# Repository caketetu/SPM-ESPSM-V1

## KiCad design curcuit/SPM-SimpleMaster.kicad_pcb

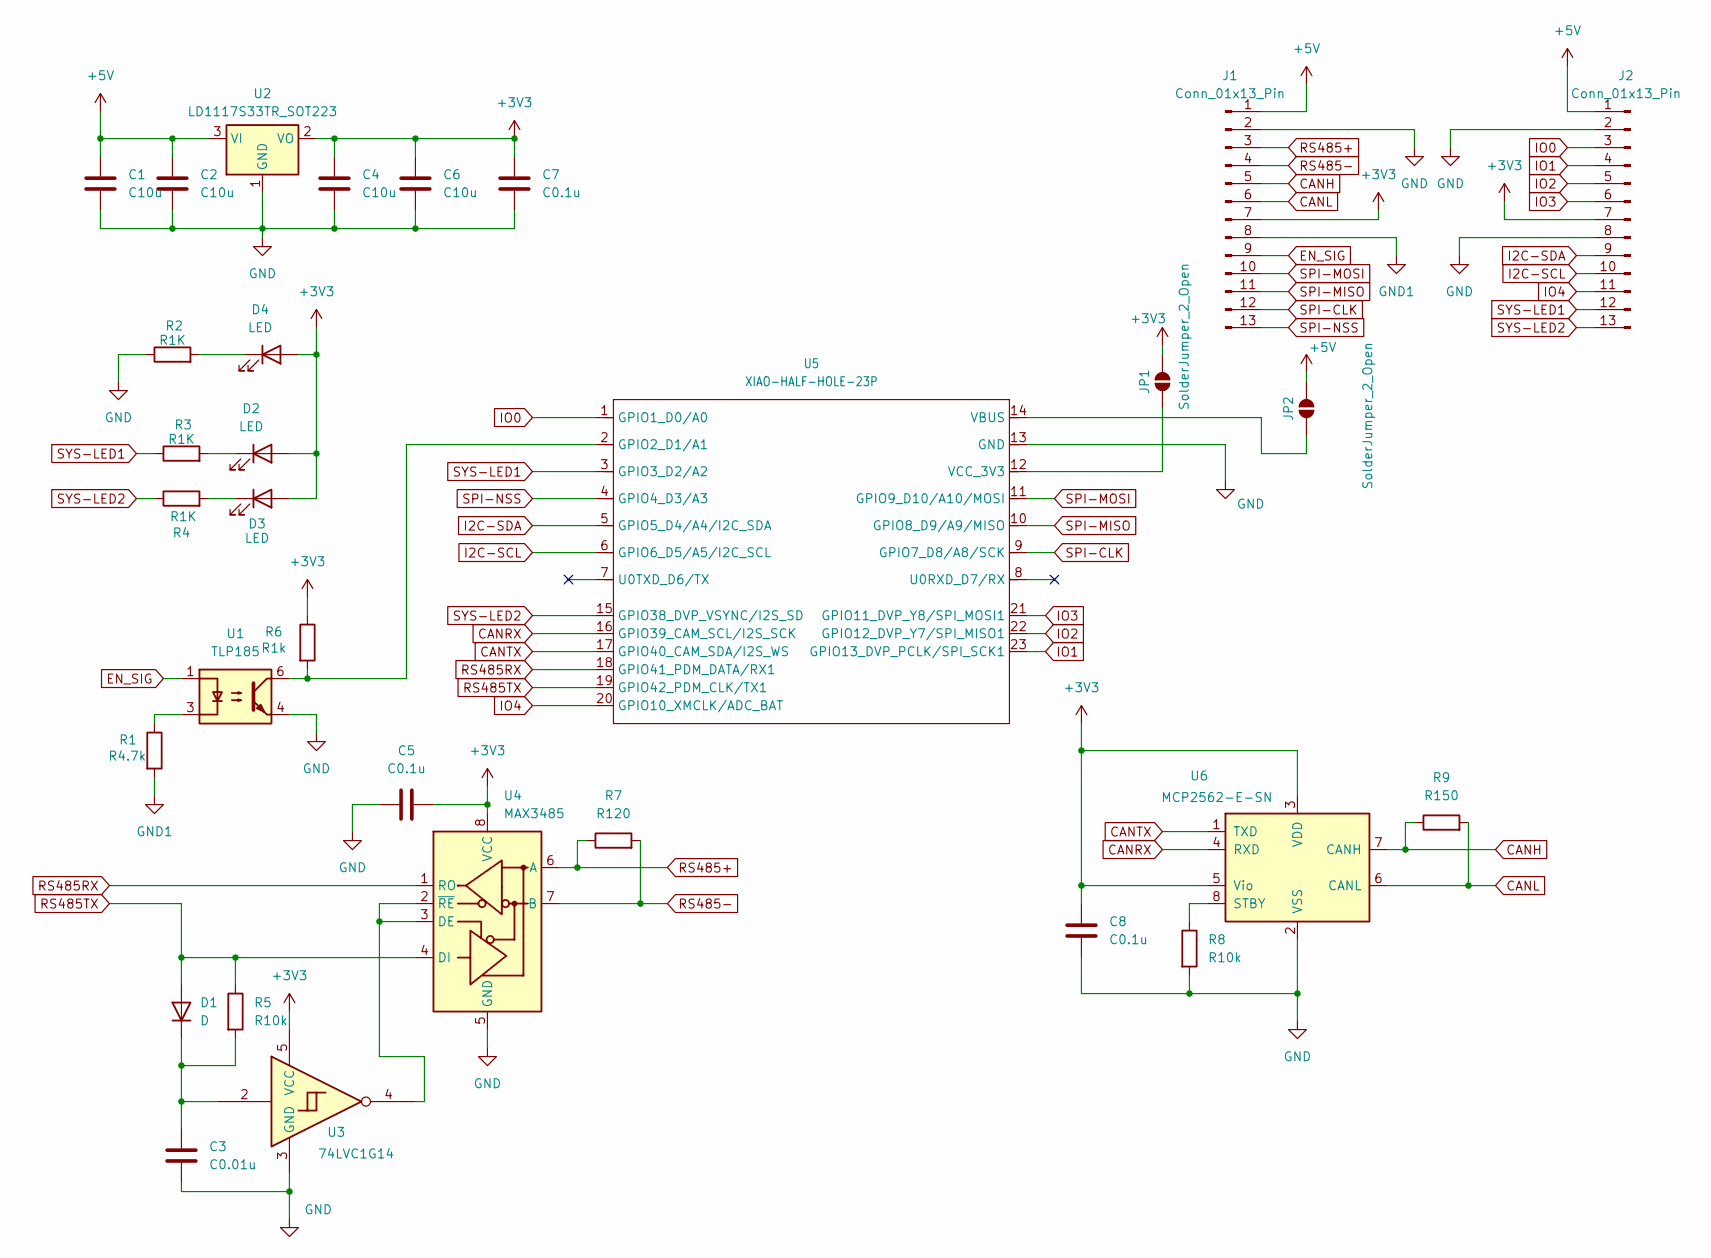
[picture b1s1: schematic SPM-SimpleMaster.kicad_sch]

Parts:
C1, C2, C4, C6: C10u; C_1206_3216Metric
C3: C0.01u; C_0805_2012Metric
C5, C7, C8: C0.1u; C_0603_1608Metric
D1: D; D_1206_3216Metric
D2, D3, D4: LED; LED_0603_1608Metric
J1, J2: Conn_01x13_Pin; PinSocket_1x13_P2.54mm_Vertical
JP1, JP2: SolderJumper_2_Open; SolderJumper-2_P1.3mm_Open_Pad1.0x1.5mm
R1: R4.7k; R_0603_1608Metric
R2, R3, R4: R1K; R_0603_1608Metric
R5, R8: R10k; R_0603_1608Metric
R6: R1k; R_0603_1608Metric
R7: R120; R_1206_3216Metric
R9: R150; R_1206_3216Metric
U1: TLP185; SOIC-4_4.55x3.7mm_P2.54mm
U2: LD1117S33TR_SOT223; SOT-223-3_TabPin2
U3: 74LVC1G14; SOT-23-5
U4: MAX3485; SOIC-8_3.9x4.9mm_P1.27mm
U5: XIAO-HALF-HOLE-23P; MOUDLE23P-SMD-2.54-21X17.8MM.kicad_mod.kicad_sym
U6: MCP2562-E-SN; SOIC-8_3.9x4.9mm_P1.27mm

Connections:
+3V3: C4.1, C5.2, C6.1, C7.1, C8.1, D2.2 (A), D3.2 (A), D4.2 (A), J1.7, J2.7, JP1.2 (B), R6.1, U2.2 (VO), U3.5 (VCC), U4.8 (VCC), U6.3 (VDD), U6.5 (Vio)
+5V: C1.1, C2.1, J1.1, J2.1, JP2.2 (B), U2.3 (VI)
CANH: J1.5, R9.1, U6.7 (CANH)
CANL: J1.6, R9.2, U6.6 (CANL)
CANRX: U5.16 (GPIO39_CAM_SCL/I2S_SCK), U6.4 (RXD)
CANTX: U5.17 (GPIO40_CAM_SDA/I2S_WS), U6.1 (TXD)
EN_SIG: J1.9, U1.1
GND: C1.2, C2.2, C3.2, C4.2, C5.1, C6.2, C7.2, C8.2, J1.2, J2.2, J2.8, R2.1, R8.2, U1.4, U2.1 (GND), U3.3 (GND), U4.5 (GND), U5.13 (GND), U6.2 (VSS)
GND1: J1.8, R1.2
I2C-SCL: J2.10, U5.6 (GPIO6_D5/A5/I2C_SCL)
I2C-SDA: J2.9, U5.5 (GPIO5_D4/A4/I2C_SDA)
IO0: J2.3, U5.1 (GPIO1_D0/A0)
IO1: J2.4, U5.23 (GPIO13_DVP_PCLK/SPI_SCK1)
IO2: J2.5, U5.22 (GPIO12_DVP_Y7/SPI_MISO1)
IO3: J2.6, U5.21 (GPIO11_DVP_Y8/SPI_MOSI1)
IO4: J2.11, U5.20 (GPIO10_XMCLK/ADC_BAT)
unnamed: C3.1, D1.1 (K), R5.2, U3.2
unnamed: D2.1 (K), R3.2
unnamed: D3.1 (K), R4.2
unnamed: D4.1 (K), R2.2
unnamed: JP1.1 (A), U5.12 (VCC_3V3)
unnamed: JP2.1 (A), U5.14 (VBUS)
unnamed: R1.1, U1.3
unnamed: U3.4, U4.2 (~RE), U4.3 (DE)
unnamed: R6.2, U1.6, U5.2 (GPIO2_D1/A1)
unnamed: R8.1, U6.8 (STBY)
RS485+: J1.3, R7.1, U4.6 (A)
RS485-: J1.4, R7.2, U4.7 (B)
RS485RX: U4.1 (RO), U5.18 (GPIO41_PDM_DATA/RX1)
RS485TX: D1.2 (A), R5.1, U4.4 (DI), U5.19 (GPIO42_PDM_CLK/TX1)
SPI-CLK: J1.12, U5.9 (GPIO7_D8/A8/SCK)
SPI-MISO: J1.11, U5.10 (GPIO8_D9/A9/MISO)
SPI-MOSI: J1.10, U5.11 (GPIO9_D10/A10/MOSI)
SPI-NSS: J1.13, U5.4 (GPIO4_D3/A3)
SYS-LED1: J2.12, R3.1, U5.3 (GPIO3_D2/A2)
SYS-LED2: J2.13, R4.1, U5.15 (GPIO38_DVP_VSYNC/I2S_SD)

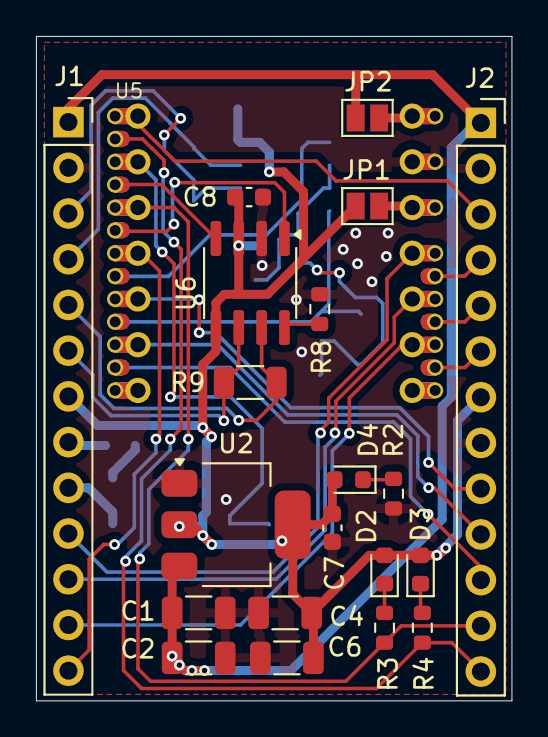
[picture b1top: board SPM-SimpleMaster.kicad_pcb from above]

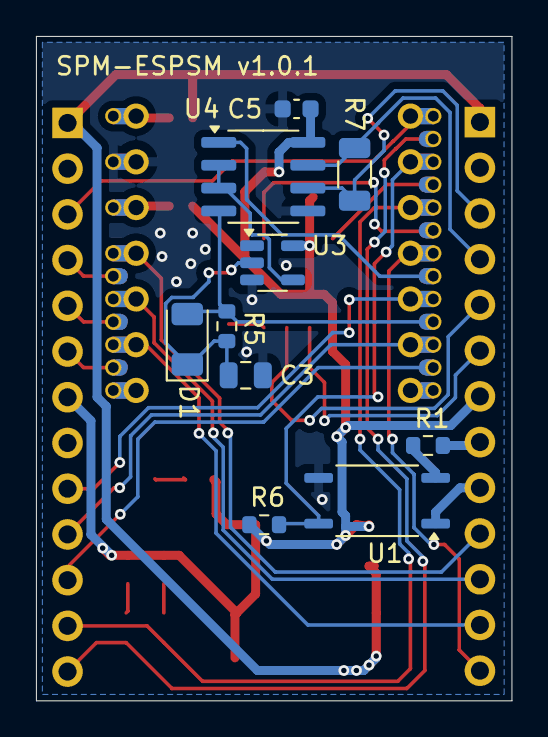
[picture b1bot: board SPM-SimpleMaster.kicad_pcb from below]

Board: 2 copper layers, 26.4 x 36.9 mm, 31 parts (10 on the bottom side), 36 nets.
